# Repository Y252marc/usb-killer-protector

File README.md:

# USB killer Protector | 🛡️ USB SHIELD | The 5kV Hard-Isolation Barrier
**Magnetic isolation. Zero physical connection. Total motherboard safety.**

👉 **[Launch Interactive Project Site](https://y252marc.github.io/usb-killer-protector/)**

---

### ⚡ The Problem: The "Spark"
USB Killers don't hack your software; they execute your hardware. By dumping high-voltage DC into your port, they fry your motherboard in milliseconds. Standard protectors are too slow.

### 🔌 The Solution: The "Moat"
I didn't just build a filter; I built a physical gap. Data is teleported across a 4.5mm "moat" using magnetic fields, while power is handled by a floating transformer. If an attacker dumps 200V into the target side, it literally has no physical path to reach your laptop.

---

### 🛠️ Hardware Loadout
* **The Brain**: **ADuM4160** Digital Isolator (Rated for **5,000V** isolation).
* **The Power**: **RFM-0505S** Isolated DC-DC Converter (Floating 5V power).
* **The Guard**: Dual **SMAJ5.0A** TVS Diodes (Clamping transients at the source).
* **The Kill Switch**: **JS202011SCQN** DPDT switch for instant manual data disconnection.

---

### 📐 Engineering Excellence
* **Split Ground Planes**: Two entirely separate copper islands—Clean vs. Dirty.
* **Differential Data Highway**: Matched D+/D- lines with 24Ω termination for zero-drop communication.
* **Pro Layout**: 2-layer FR4 with 2mm rounded edges for a clean, crack-proof finish.

### 📂 Inside the Repo
* **3D Assets**: STEP models for the isolator, transformer, and ports.
* **Production**: Factory-ready Gerber and Drill files.
* **Source**: Full KiCad 9 design project.

---

### 📜 License
This project is licensed under the **MIT License** - see the [LICENSE](LICENSE) file for details.

### ⚠️ Disclaimer
*Testing destructive hardware is dangerous. This shield is for research and educational vibes only. Use it at your own risk.*

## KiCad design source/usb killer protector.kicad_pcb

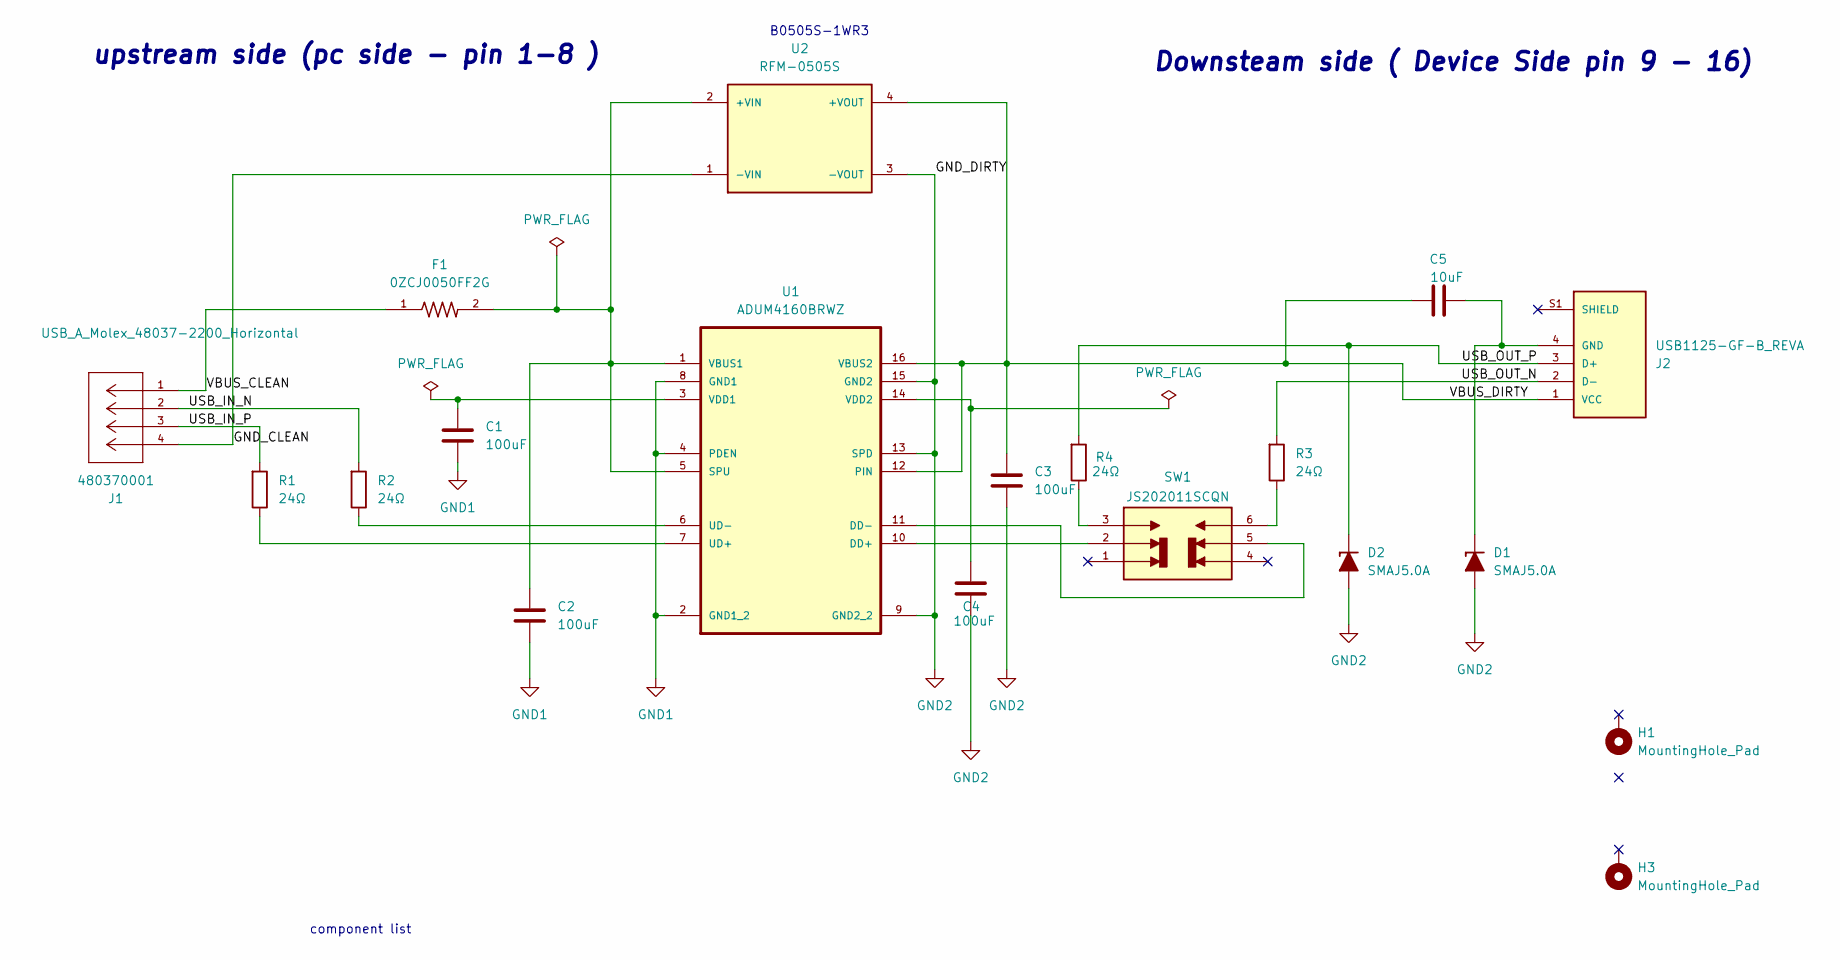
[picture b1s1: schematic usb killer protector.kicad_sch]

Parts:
C1, C2, C3, C4: 100uF; C_0805_2012Metric
C5: 10uF; C_1206_3216Metric
D1, D2: SMAJ5.0A; D_SMA
F1: 0ZCJ0050FF2G; RESC3216X125N
H1, H3: MountingHole_Pad; MountingHole_3.2mm_M3_Pad_Via
J1: 480370001; USB_A_Molex_48037-2200_Horizontal; MANUFACTURER_PART_NUMBER 480370001
J2: USB1125-GF-B_REVA; GCT_USB1125-GF-B_REVA; PARTREV A
R1, R2, R3, R4: 24Ω; R_0805_2012Metric
SW1: JS202011SCQN; SW_JS202011SCQN; PARTREV 26 May 22
U1: ADUM4160BRWZ; SOIC127P1032X265-16N; MPN ADUM4160BRWZ
U2: RFM-0505S; CONV_RFM-0505S; PARTREV 0

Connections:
/GND_CLEAN: J1.4, U2.1 (-VIN)
/USB_IN_N: J1.2, R2.1
/USB_IN_P: J1.3, R1.1
/USB_OUT_N: J2.2 (D-), R3.1
/USB_OUT_P: D2.1 (K), J2.3 (D+), R4.1
/VBUS_CLEAN: F1.1, J1.1
/VBUS_DIRTY: C3.1, C5.1, J2.1 (VCC), U1.12 (PIN), U1.16 (VBUS2), U2.4 (+VOUT)
GND1: C1.2, C2.2, U1.2 (GND1_2), U1.4 (PDEN), U1.8 (GND1)
GND2: C3.2, C4.2, D1.2 (A), D2.2 (A), U1.9 (GND2_2), U1.13 (SPD), U1.15 (GND2), U2.3 (-VOUT)
unnamed: C5.2, D1.1 (K), J2.4 (GND)
unnamed: R3.2, SW1.6
unnamed: R4.2, SW1.3
unnamed: SW1.2, U1.10 (DD+)
unnamed: SW1.5, U1.11 (DD-)
unnamed: C2.1, F1.2, U1.1 (VBUS1), U1.5 (SPU), U2.2 (+VIN)
unnamed: R1.2, U1.7 (UD+)
unnamed: R2.2, U1.6 (UD-)
unnamed: C1.1, U1.3 (VDD1)
unnamed: C4.1, U1.14 (VDD2)

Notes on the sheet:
B0505S-1WR3
Downsteam side ( Device Side pin 9 - 16)
component list
upstream side (pc side - pin 1-8 )

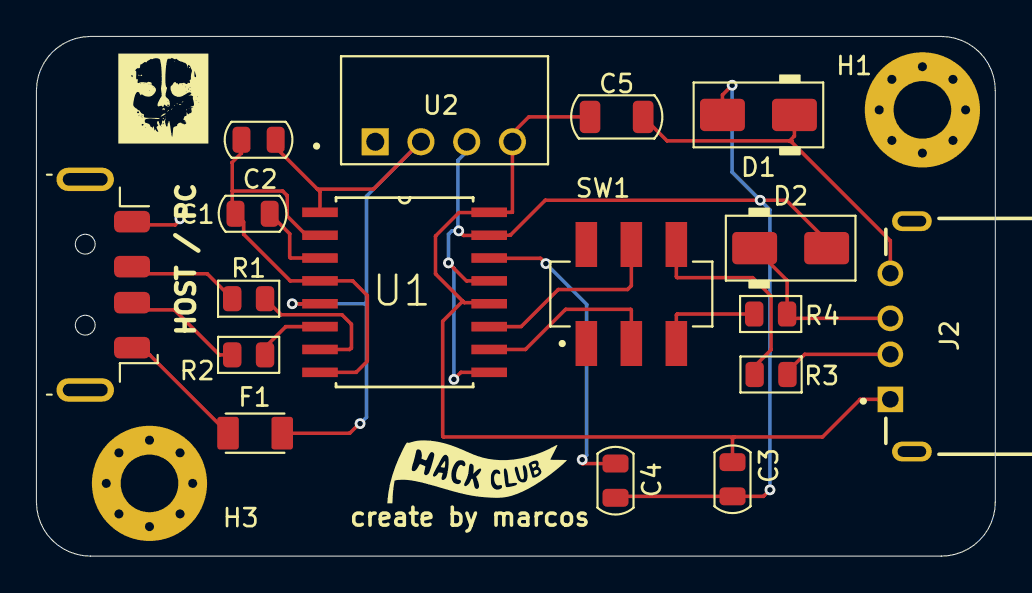
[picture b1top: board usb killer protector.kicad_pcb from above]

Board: 2 copper layers, 53.3 x 28.9 mm, 19 parts (0 on the bottom side), 19 nets.

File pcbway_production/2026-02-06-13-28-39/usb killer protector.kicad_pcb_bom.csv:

Designator,Quantity,Value,Footprint,Package,MPN,DNP,Mount_Type,Description,MF,Description_1,Price,SnapEDA_Link,MP,Availability,Check_prices,MFR_NAME,MANUFACTURER_PART_NUMBER,MAXIMUM_PACKAGE_HEIGHT,STANDARD,PARTREV,MANUFACTURER,SNAPEDA_PN,OC_FARNELL,SUPPLIER,OC_NEWARK
"C1, C2, C3, C4",4,100uF,C_0805_2012Metric,,,,smt,"SMD 0805 MLCC capacitor, Alternate KiCad Library",,,,,,,,,,,,,,,,,
C5,1,10uF,C_1206_3216Metric,,,,smt,"SMD 1206 MLCC capacitor, Alternate KiCad Library",,,,,,,,,,,,,,,,,
"D1, D2",2,SMAJ5.0A,D_SMA,,,,smt,"SMA Unidirectional TVS diode, 5V, 400W, Alternate KiCAD Library",,,,,,,,,,,,,,,,,
F1,1,0ZCJ0050FF2G,RESC3216X125N,1206 Bel Fuse,,,smt,,Bel Fuse,1206 SMT PPTC | 0.50 Ih | 8V,None,https://www.snapeda.com/parts/0ZCJ0050FF2G/Bel+Circuit+Prote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,0ZCJ0050FF2G,In Stock,https://www.snapeda.com/parts/0ZCJ0050FF2G/Bel+Circuit+Prote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,,,,,,,,,,
J1,1,480370001,USB_A_Molex_48037-2200_Horizontal,None,,,smt,,Molex,"USB-A (USB TYPE-A) USB 2.0 Plug Connector 4 Position Through Hole, Right Angle",None,https://www.snapeda.com/parts/480370001/Molex/view-part/?ref=snap,480370001,In Stock,https://www.snapeda.com/parts/480370001/Molex/view-part/?ref=eda,Molex Connector Corporation,480370001,,,,,,,,
J2,1,USB1125-GF-B_REVA,GCT_USB1125-GF-B_REVA,None,,,tht,,Global Connector Technology,"USB 2.0 Receptacle, Type A, Through Hole, Horizontal, Top Mount, Without Flange, 6.48mm profile, 4 Pins, Through hole, compact receptacle, 5000 mating cycle, full size",None,https://www.snapeda.com/parts/USB1125-GF-B/Global+Connector+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,USB1125-GF-B,In Stock,https://www.snapeda.com/parts/USB1125-GF-B/Global+Connector+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,,,6.63mm,Manufacturer Recommendations,A,GCT,,,,
"R1, R2, R3, R4",4,24Ω,R_0805_2012Metric,,,,smt,"SMD 0805 Chip Resistor, European Symbol, Alternate KiCad Library",,,,,,,,,,,,,,,,,
SW1,1,JS202011SCQN,SW_JS202011SCQN,None,,,smt,,C&K,Slide Switch DPDT Surface Mount,None,https://www.snapeda.com/parts/JS202011SCQN/C%2526K/view-part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,JS202011SCQN,In Stock,https://www.snapeda.com/parts/JS202011SCQN/C%2526K/view-part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,,,5.5 mm,Manufacturer Recommendations,26 May 22,C&K,JS202011SCQN,,,
U1,1,ADUM4160BRWZ,SOIC127P1032X265-16N,SOIC-16,ADUM4160BRWZ,,smt,,Analog Devices,Full/Low Speed USB Digital Isolator,None,https://www.snapeda.com/parts/ADUM4160BRWZ/Analog+Devices/vi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,ADUM4160BRWZ,In Stock,https://www.snapeda.com/parts/ADUM4160BRWZ/Analog+Devices/vi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,,,,,,,,1858056,Analog Devices,24R8652
U2,1,RFM-0505S,CONV_RFM-0505S,SIP-4 Recom Power,,,tht,,Recom Power,"DC-DC Converter, SIP4, 1kV unreg, Single Output, 1W, 5V Out, RFM Series | RECOM Power Inc. RFM-0505S",None,https://www.snapeda.com/parts/RFM-0505S/Recom+Power/view-par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,RFM-0505S,In Stock,https://www.snapeda.com/parts/RFM-0505S/Recom+Power/view-par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,,,10mm,Manufacturer Recommendations,0,Recom,,,,

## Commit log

2026-02-11 initial release: pcb design and schematic complete
2026-02-11 uppdates
2026-02-11 bom file added
2026-02-11 Rename index.html to docs/index.html
2026-02-11 Enhance README with project overview and specifications
    Added detailed project description and features to README.
